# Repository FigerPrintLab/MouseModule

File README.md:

# MouseModule [WORK IN PROGRESS]

This is an eurorack module that processes mouse events through the [Raspberry Pi](https://www.raspberrypi.org/) and generates some analog signals. It offers also recording and playback capabilities with more complex mice.

## Build instructions 

This is a pretty simple module to build and try if you have a Raspberry Pi.

### Hardware

Inside the repository (in the KiCad folder) you'll find the schematic (the PCB is still WIP) that you can use to build a very simple prototype on a breadboard. All you need are some passive components, a general purpose opamp and a comparator (used as level translator from 3.3V to 5V).  
GPIO 4 can be tied to an LED to get visual feedback when you're recording. Same for GPIO 17 which signals that you're playing back the recorded events.

### Software

The program is written in C and it captures all the relevant mouse events in order to generate the appropriate hardware signals on specific GPIOs (listed below). The software should be run on the minimal version of the Pi OS (Raspberry Pi OS Lite) because of the lack of a graphical server which could behave weirdly with the mouse events. In order to compile it you need to install the [`pigpio` library](https://abyz.me.uk/rpi/pigpio/) which requires privileged permissions to run.

```sh
# clone the repository
git clone https://github.com/FingerprintLab/MouseModule.git
cd MouseModule

# install the dependency
sudo apt update && sudo apt upgrade -y
sudo apt install -y pigpio

# compile
cd Software
make

# run
sudo ./main
```

## Features

These are the main features of the module:

- Mouse position -> 2 analog signal for each coordinate
- Left button -> Trigger
- Right button -> Gate
- Middle button -> Change mode (attenuation or offset)
- Wheel -> Increase/decrease attenuation or offset (based on current mode)
- Extra button -> Start/stop the recording
- Side button -> Erase the recording

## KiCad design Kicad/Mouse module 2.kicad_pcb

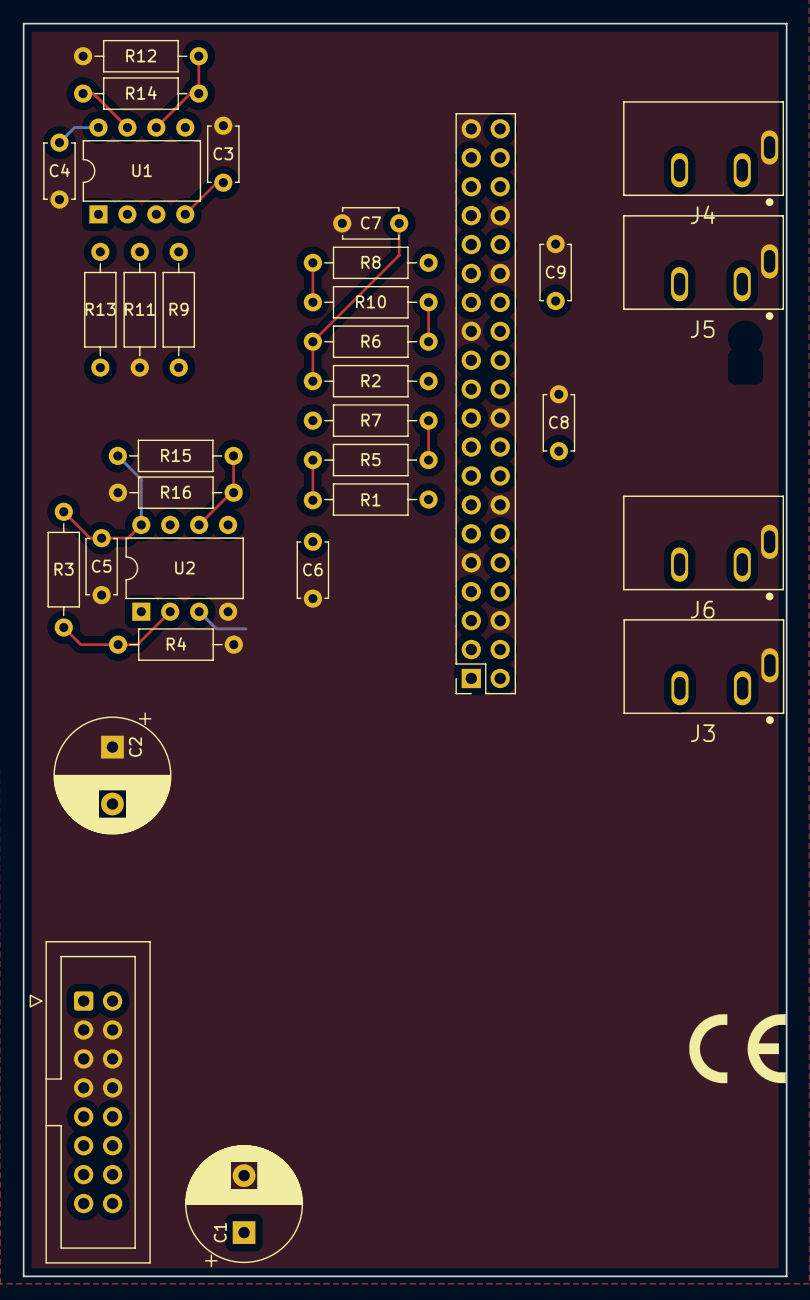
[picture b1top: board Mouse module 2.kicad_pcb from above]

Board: 2 copper layers, 67.0 x 110.0 mm, 33 parts (0 on the bottom side), 22 nets.

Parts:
C1, C2: 1uF; CP_Radial_D10.0mm_P5.00mm
C3, C4, C5, C6, C7, C8, C9: 0.1uF; C_Disc_D4.7mm_W2.5mm_P5.00mm
J1: Conn_02x20_Odd_Even; PinSocket_2x20_P2.54mm_Vertical
J2: 02x08_IDC; IDC-Header_2x08_P2.54mm_Vertical
J3: GATE; CUI_SJ1-3533
J4: X; CUI_SJ1-3533
J5: Y; CUI_SJ1-3533
J6: TRIG; CUI_SJ1-3533
R1, R2, R3, R5, R6, R15: 10k; R_Axial_DIN0207_L6.3mm_D2.5mm_P10.16mm_Horizontal
R4, R16: 4.7k; R_Axial_DIN0207_L6.3mm_D2.5mm_P10.16mm_Horizontal
R7, R8: 670; R_Axial_DIN0207_L6.3mm_D2.5mm_P10.16mm_Horizontal
R9, R10: 150k; R_Axial_DIN0207_L6.3mm_D2.5mm_P10.16mm_Horizontal
R11, R12: 15k; R_Axial_DIN0207_L6.3mm_D2.5mm_P10.16mm_Horizontal
R13, R14: 37k; R_Axial_DIN0207_L6.3mm_D2.5mm_P10.16mm_Horizontal
U1: TL072; DIP-8_W7.62mm
U2: LM393; DIP-8_W7.62mm

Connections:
+5V: C5.2, J1.2, J1.4, J2.12, R3.2, R15.2, U2.8
+12V: C1.1, C4.2, J2.10, U1.8
-12V: C2.2, C3.2, J2.2, R9.1, R10.1, U1.4
GND: C1.2, C2.1, C3.1, C4.1, C5.1, C6.1, C7.1, C8.1, C9.1, J1.6, J1.9, J1.14, J1.20, J1.25, J1.30, J1.34, J1.39, J2.3, J2.4, J2.5, J2.6, J2.7, J2.8, J3.S, J4.S, J5.S, J6.S, R4.1, R11.1, R12.1, R16.1, U2.4
unnamed: C6.2, R1.1, R5.2
unnamed: C7.2, R2.1, R6.2
unnamed: C8.2, R5.1, R7.2
unnamed: C9.2, R6.1, R8.2
unnamed: J3.T, U2.1
unnamed: J4.T, R13.1, U1.1
unnamed: J5.T, R14.1, U1.7
unnamed: J6.T, U2.7
unnamed: R3.1, R4.2, U2.2
unnamed: R7.1, R9.2, U1.3
unnamed: R8.1, R10.2, U1.5
unnamed: R11.2, R13.2, U1.2
unnamed: R12.2, R14.2, U1.6
unnamed: R15.1, R16.2, U2.6
RB_GATE: J1.29, U2.3
RB_TRIG: J1.31, U2.5
RB_X: J1.12, R1.2
RB_Y: J1.33, R2.2

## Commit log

2021-08-04 minor upgrades
2021-08-04 added favicon.ico
2021-08-04 some other minor fixes
2021-08-04 removed serve-favicon dependency
2021-08-05 added module for raspberry's functions
2021-08-05 multiple POST routes & lower decimal precision of mouse position
2021-08-05 general cleanup & dual TL072
2021-08-05 ready for nginx
2021-08-05 commented out a debug line
2021-08-13 cleaning some secondary files
2021-11-29 work on PCB & added some LEDs
2021-11-29 minor software corrections
2021-11-29 update package-lock.json by npm install
2021-11-29 software control of record and playback LEDs
2021-11-30 longer trigger pulse
2022-03-13 Added pwm experiment
2022-03-14 added pwm module & cleanup
2022-03-16 cleanup & pwm read & gpio
2022-03-16 succesfull pwm test
2022-03-16 removed pwm & gpio files in favor of pigpio lib
2022-03-18 WIP: integrating gpio control in event.c
2022-03-18 reinitialize on every playback cycle
2022-03-18 cleanup
2022-03-18 no more 'make clean' error
2022-03-19 hw signals achieved & removed GATE bug on some mice
2022-03-19 achieved attenuation & offset logic
2022-03-20 achieved movement constrain on attenuation/offset & removed playback timing bug
2022-03-20 removed useless files
2022-03-20 updated Kicad files
2023-08-21 update KiCad version
2023-09-07 added LCD code
2023-09-07 fixed README typos
